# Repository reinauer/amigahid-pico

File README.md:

# amigahid-pico

please note: the interesting stuff goes into the [development](https://github.com/borb/amigahid-pico/tree/development) branch, so if main seems slow, check it out.

## introduction

amigahid-pico uses the rp2040 microcontroller (e.g. the raspberry pi pico) in a carrier board to attach usb input devices to a standard amiga without the need for a usb stack on the amiga itself.

it currently supports keyboards and mice and provides connection via the internal keyboard connector, the rj11/din socket on big-box amigas, and via the controller ports.

**this project is very much a work in progress.**

## **important note**

* r7 uses the native RP2350A/RM2 board and an ALPS menu lever. See [r7 firmware setup](./doc/installation.md#rev7-rp2350a-and-rm2) and [lever controls](./doc/runtime-configuration.md#rev7-menu-lever).
* for r5/r6 carriers on the `features` branch, select `BOARD_HIDPICO_REV5` to enable both controller ports: port 1 defaults to mouse and port 2 to USB joystick. REV4 firmware supports the same keyboard and first port, but leaves the second port unused. see [USB joystick mode](./doc/joystick.md).

* **always read the [errata](./doc/errata.md) section for the current pcb layout before deciding whether or not to build.**

## documentation

* [installation](./doc/installation.md)
* [hardware](./doc/hardware.md)
* [errors in revisions (errata)](./doc/errata.md)

## history

this project is a rewrite of the [amigahid](https://github.com/borb/amigahid) project to the rp2040 microcontroller.

originally, after the retirement of the arduino adk board and shortening availability of the max3421e "usb host shield" for arduino boards, the need for a cheap, easy and continually available replacement was sought.

at first, the uhs mini via a level shifter seemed ideal, but significant issues were found convincing it to work with a variety of arduino boards.

the rp2040 made sense as a target because it is widely available, has sufficient physical connections and is powerful enough to meet multiple needs.

## what is the latency of this?

i have not measured the latency, but the keyboard signals are sent out the moment they are received on the usb bus. the potential latency is likely fractionally longer than the amiga mcu but bear in mind the rp2040 is significantly faster than the standard amiga keyboard controller.

## roadmap

please see the issues tab on the [github repository](https://github.com/borb/amigahid-pico) for the current list of planned features. the tl;dr is:

normal:
* i<sup>2</sup>c display for config/status
* controller emulation
    * keyboard-based controller emulation (use udlr for directions?)
* flash memory-based configuration
* possible amiga-side control panel (using bidirectional controller port signals)
* rotary control simulation (for controlling gotek drives)

crazy talk:
* non-amiga support
* non-hidbp support
* analogue/paddle emulation
* fix some tinyusb issues (hotplug, timing-related instability)

## license

on the fence at the moment, but the current license choice is Eclipse Public License 2.0 (EPL-2.0).

## third party licenses

* µgui: this code contains 'µgui' by achim döbler; the license for this can be read at in the [display readme](./src/display/README.md)

## whuh... who?

nine <[nine@aphlor.org](mailto:nine@aphlor.org)>

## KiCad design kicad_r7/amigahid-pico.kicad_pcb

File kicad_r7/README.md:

# AmigaHID r7 — hardware prototype

Copied from `kicad_r6`. **Prepared for a factory quotation and prototype CAM
review; not released for manufacture.** The r6 project is unchanged.

## Current design

- **70 × 66 mm**, four copper layers, nominal 1 mm PCB. The bounding rectangle is
  2.9% smaller than r6's 70 × 68 mm board. All assembled components are on top.
  The DB9 edge extends 6 mm under the housings; KiCad Y now spans -6..60 mm,
  retaining all component and route coordinates.
- Bare RP2350A, 4 MB Winbond QSPI flash, and left-facing RMC20452T / RM2 radio.
- Centered 35.5 × 33.7 mm OLED, two DE9 ports, mini-DIN keyboard and two stacked
  USB-A ports. The CH334P hub uses two of its four downstream channels.
- USB-C and a side-actuated RECOVERY switch at the bottom right.
- H1–H4 are shared OLED/base/main-PCB mounts. H5/H6, the A500 header, extra power
  header and selector jumper are removed. UART/SWD use bare pads.
- Five-sheet schematic: interfaces, controller, power, USB, and control.

Open [the KiCad project](amigahid-pico.kicad_pro). The normal editable design is
[the schematic](amigahid-pico.kicad_sch) and [the PCB](amigahid-pico.kicad_pcb).
The matching enclosure is in [`../case_r7`](../case_r7/README.md).

## Power and recovery

Mini-DIN pin 4 remains a 5 V power input. The TPS2116 automatically gives
USB-C priority and falls back to the keyboard supply when USB-C is removed.
It has reverse-current blocking, so the two supplies are not directly joined.
See the [TPS2116 datasheet](https://www.ti.com/lit/ds/symlink/tps2116.pdf).
The DE9 5 V pins remain unconnected. No power-selection jumper is needed.

The [A4000 user guide, appendix B-8](https://device.report/m/e9fdb1a480863f0ee437f3aaf1a4cf073445989ed93d380fc9f8956629044f95.pdf#page=85)
rates keyboard power at **100 mA**. The user's current revision operates from
this port; r7 preserves that option, but its new MCU, hub, radio, display and
peripherals require a fresh current measurement. The 500 mA hold PTC is shared
by both USB-A ports and does not establish available Amiga current.

USB-C can also power normal operation from an adequately rated 5 V supply.
Use a supply rated for at least 1 A for prototype testing. This board does not
negotiate USB PD or read Type-C current advertisements. A PC's unconfigured
USB port is not a guaranteed normal-operation power source: hold RECOVERY
before connecting a PC for service. Keyboard-only operation must stay within
the actual Amiga/cable budget; adding USB-C power does not raise that rating.

| State | Action and result |
|---|---|
| Amiga off, PC recovery | Hold RECOVERY, connect USB-C, wait at least 0.1 s, release. |
| USB-C already connected | Press/release RECOVERY to enter ROM recovery. |
| Normal operation from USB-C supply | Connect power without holding RECOVERY. |
| Return to keyboard-powered operation | Remove USB-C, then press/release RECOVERY to reboot normally. |
| Return to USB-C-only normal operation | Unplug/reconnect USB-C without holding RECOVERY. |

Recovery is implemented in hardware. RECOVERY_N low presets the SN74HCS74 latch;
Q2 pulls QSPI-CS low through R6, U7 selects the PC data path, and U11 removes
USB-A power. The Amiga signal switches are disabled whenever keyboard power
is absent or recovery is selected. Thus invalid application flash does not
prevent button-based ROM recovery. This assumes normal RP2350 OTP settings;
permanently disabling ROM USB boot in OTP is outside this prototype design.

U13 (TPS3808G33DBVR) monitors the shared 3.3 V rail and holds RUN low
until the rail exceeds its nominal 3.07 V threshold and the reset-release
delay expires. CT is intentionally unconnected for a nominal 20 ms delay.
C41 provides local 100 nF bypassing; R12 remains the 10 kΩ RUN pull-up.
This allows the external flash to power up before the MCU starts its boot ROM.

The switch grounds RECOVERY_N, pulled up by R26 (10 kΩ). This net drives
both U13's manual-reset input and U9's preset input. U13's automatic reset
output drives RUN only, so cold-start and brownout resets do not themselves
request BOOTSEL. Button release also receives the supervisor's reset delay.
The recovery latch still retains the requested USB mode after release.

The latch uses Schmitt inputs and a separate 100 kΩ/100 nF clear delay. U12 translates
USB VBUS to 3.3 V with power-off protection. At power-up with the button held,
both asynchronous latch inputs can be asserted: the documented state has
both outputs high, while U13 holds RUN low to keep the MCU reset and D2 keeps USB-A power off.
Hold the button until the clear delay has expired, then release. The same
button without USB-C performs a normal reset. There is no firmware timing or
double-tap dependency.

U11 ramps the 220 µF host reservoir with 10 nF on CT (about 26.6 ms typical
10–90% rise at 5 V). Reservoir charging is about 33 mA over that interval,
before peripheral load and tolerances. Recovery leaves this branch off.
Direct USB-C bypass is 4.7 µF + 100 nF; the mux soft-starts the main board
supply. Check actual inrush, recovery current and USB suspend behavior on the
first assembled board. No USB compliance certification is implied.

## Placement and capacitor review — 2026-10-14

The required connectors and OLED stay fixed. U2 moved toward the first DE9
connector; U3 now occupies the MCU's right side. U8 was moved and rotated toward
the stacked USB-A connector. Pull-up arrays and local bypass parts were moved
with the signal groups. The signal-net minimum-spanning-tree estimate fell
from 1904 to 1607 mm (15.6%); this is a placement metric, not measured routed
length, timing or signal-integrity proof.

Most resistors and local bypass capacitors are already **0402**. The OLED
pull-ups and several inherited bypass capacitors use **0603**. The 10 µF supply
capacitors remain **0805**. Replacing all 0805 parts with 0603 would save little
board area and can reduce effective capacitance at operating voltage.

For C10/C11, Samsung's typical 25°C DC-bias curves give:

| Part | Package / rating | Effective pair capacitance at 3.3 V |
|---|---|---|
| Former C59461, CL10A226MQ8NRNC | 0603, 22 µF / 6.3 V | about 19.5 µF |
| Selected C45783, CL21A226MAQNNNE | 0805, 22 µF / 25 V | about 29.8 µF |

These typical values exclude initial tolerance, temperature and aging; they
are not guaranteed minima. The larger parts provide more transient margin.
Sources: [Samsung 0603 curves](https://product.samsungsem.com/mlcc/CL10A226MQ8NRN.do),
[Samsung 0805 curves](https://product.samsungsem.com/mlcc/CL21A226MAQNNN.do), and
[AP63203 application guidance](https://www.diodes.com/datasheet/download/AP63200-AP63201-AP63203-AP63205.pdf).
C3's displayed voltage was also corrected to 25 V to match its existing C15850
part number.

### USB-A bulk capacitor

150 µF is a sensible nominal value: at −20% initial tolerance it gives 120 µF.
The USB hub guidance calls for at least 120 µF of low-ESR reservoir capacitance
per hub; that can be shared by these two adjacent ports on the same power rail.
See [Microchip AN17](https://www.microchip.com/content/dam/mchp/documents/OTH/ApplicationNotes/ApplicationNotes/AN17-APID.pdf).

The former RVT standard electrolytic's supplier table leaves the ESR limit
blank. C4 is upgraded to **220 µF / 10 V polymer, C19270700**, with
specified **35 mΩ at 100 kHz**, in approximately the same 6.6 mm square body
area. Its initial minimum capacitance is 176 µF. It is listed at $0.1657 each
at quantity 5 ($0.1302 at 50), before shipping/taxes, checked 2026-10-14.
[Supplier part](https://www.lcsc.com/product-detail/C19270700.html),
[manufacturer family datasheet](https://datasheet.lcsc.com/datasheet/pdf/25cd8a66a5cec751f287aca4fb3a3d5c.pdf?productCode=C19270700).

C4 remains between the keyboard and stacked USB connectors: their spacing
leaves room for it, and its supply connection can run beside the USB connector.
It does not obstruct the OLED. Rotating the original capacitor into the narrow
gap caused courtyard conflicts; the horizontal orientation is retained.
The supplier lists 5.8 mm height, while the family table shows a 7 mm variant;
confirm the exact ordered part. The case clearance model uses 8 mm, also
covering the 7.72 mm height of the supplier's STEP model.

### Two 12 MHz crystals

Y1 is the RP2350A clock reference and Y2 is the CH334P USB hub reference.
Each passive crystal belongs to a separate on-chip oscillator. Connecting one
crystal to both oscillators is not a valid replacement. A common active clock
would need a clock distribution and startup design; using an MCU-generated
clock would also couple hub operation to firmware/reset behavior.

The WCH datasheet section 6.2 describes a crystal-free mode, but says some
parameters may depart from USB requirements and availability depends on the
ordered variant. Both crystals are retained by the 2026-10-14 design decision.
WCH's v2.91 datasheet specifies approximately 16 pF internally on each XI/XO
pin and recommends no external load capacitors. Matching the selected
10 pF-load crystal still requires allowance for board and pin capacitance.
Sources: [WCH datasheet](https://www.wch.cn/downloads/CH334DS1_PDF.html)
and [RP2350 reference design](https://datasheets.raspberrypi.com/rp2350/hardware-design-with-rp2350.pdf).
C5 provides local 3.3 V ceramic bypass near the USB service circuitry.

A lower-ESR capacitor helps hot-plug droop, but also changes charging inrush.
Measure both USB hot-plug behavior and startup through the actual Amiga cable.
The larger reservoir is behind U11, which disconnects it during recovery.

### Smaller flash option

A 4 × 3 mm USON flash, **W25Q32JVUUIQ / C2999380**, could replace the current
SOIC-8 flash without reducing the 4 MB capacity. Current LCSC listings put it
at about $2.53 versus $1.65 for the selected C5355146 at quantity 1, or $1.91
versus $1.17 at quantity 100. It saves package area but increases BOM cost and
requires a new footprint and routing. The SOIC part is retained because it fits.
Sources: [SOIC flash](https://www.lcsc.com/product-detail/C5355146.html) and
[USON flash](https://www.lcsc.com/product-detail/C2999380.html), checked 2026-10-14.

## Sourcing and footprint provenance

[BOM.csv](BOM.csv) and [SOURCING.csv](SOURCING.csv) list **110 assembled parts** (45 unique LCSC codes).
Every purchased schematic part has an `LCSC Part #` field. Holes and bare test
pads are non-BOM geometry and have no part number. The OLED module and enclosure
hardware are external assemblies, as in r6; the PCB BOM includes J3.
`assembly-accessories.json` specifies the retained r6 SH1106 module and mounting
hardware. The r6 records give its drawings and pinout, but no manufacturer
part number or LCSC code; do not invent a purchasing code or substitute a
GND-first module.

`lcsc.pretty` contains LCSC/EasyEDA imports plus supplier-drawing corrections.
Original imports are retained in `vendor-originals`. The DE9 footprint was
reconstructed from its LCSC supplier drawing because no usable imported model
was available. The local `r7.pretty` library also contains the reset supervisor
and ALPS menu-switch footprints.

Corrections are reproducible in `scripts/prepare_libraries.py`: RM2 pad geometry
and antenna keepout, connector shield pin numbers, USB-C combined power lands,
NPTH locating pegs, stacked USB shield row pitch, and four paste apertures on
the RP2350 exposed land. The MCU's local regulator/decoupling topology follows
the official [RP2350 hardware design reference](https://datasheets.raspberrypi.com/rp2350/hardware-design-with-rp2350.pdf);
its reference PCB and license are in `reference/`.

Factory assembly was selected on 2026-10-14. The public JLC assembly stock
snapshot in [assembly-stock-check.json](assembly-stock-check.json) covers all
43 of the 45 part numbers and records stock at that check. The supervisor
and menu switch need a fresh availability check. Direct retail stock is recorded
separately in [stock-check.json](stock-check.json). Retail unavailability is
not the same as unavailability in the assembler's inventory. These snapshots
are dated evidence, not reserved material or an accepted assembly quote.

| Item | Selected LCSC part | JLC public stock on 2026-10-14 |
|---|---|---:|
| Stacked USB-A | C2341 | 3,310 |
| Mini-DIN | C77848 | 2,060 |
| Two female DE9 connectors | C50380980 | 1,711 |
| RM2 radio | C49451547 | 117 |
| RP2350 regulator inductor | C42411119 | 75 |
| Recovery latch | C2866652 | 619 |

The r6 HOOYA DIN-603 / C7428703 really was stocked in the earlier snapshot.
It now has zero direct LCSC stock and only one in public JLC stock, below the
listed placement minimum. J7 uses **CONNFLY DS1093-01-PN60 / C77848** instead.
Its drawing specifies 1.1 mm signal holes, 2.3 mm shield holes and 13.7 mm shield
spacing. The front face stays at the existing case opening. The supplier
footprint needed corrections to shield-hole size and central-tab position;
these are recorded in `scripts/adopt_connfly_din.py`. C54573054 is a larger
full-size DIN connector, so it is not a substitute for this mini-DIN socket.

Keep the exact Abracon L1: winding polarity is part of the RP2350 regulator
reference layout. The factory's small stock count needs reconfirmation before
ordering. Do not substitute an arbitrary 3.3 µH inductor.

R9's LCSC number was corrected from C25118 (47 Ω) to **C25117 (470 Ω)** to
match the RM2 DOUT-combining circuit. The other selected resistor/capacitor
values were compared with supplier descriptions. D4–D6 add ground-referenced
TPD2EUSB30 ESD protection at both USB-A channels and the USB-C service channel;
these add about $2.05 in initial-tier parts cost. U2/U3 remain cost-review
candidates, but a substitute must retain 5 V signal handling, 3.3 V translation
and specified power-off isolation.

### Stacked USB-A availability and fit

The selected J4 **907-111A1012D10200 / C2341** is available: the direct LCSC
page checked on 2026-10-14 lists **3,310 immediately shippable units**, minimum
and order multiple five, at **$0.1855 each for five** before discounts,
shipping and taxes. The earlier out-of-stock sourcing note has been corrected.
[LCSC listing](https://www.lcsc.com/product-detail/C2341.html).

The board has the drawing's 13.10 mm shield-column pitch, 5.80 mm shield-row
pitch and 2.60 mm contact-row pitch. Shield holes are 2.30 mm; all eight contact holes now use the drawing's
0.92 mm recommendation. The 14.60 mm body width excludes the wider 15.50 +/- 0.20 mm
features. The case opening is now 16.90 mm wide, allowing 0.60 mm per side around
the 15.70 mm maximum envelope. Check retention on the 1 mm PCB too.
[Supplier drawing](https://datasheet.lcsc.com/datasheet/pdf/a0b416dc2d0ad40e281371fbd00e5e99.pdf?productCode=C2341).

The supplier drawing calls the housing high-temperature thermoplastic, while
the LCSC Chinese product description says it is not high-temperature rated.
Neither establishes a soldering temperature/time profile. Plan separate
through-hole assembly after SMT reflow unless the supplier confirms a suitable
profile. [LCSC Chinese listing](https://item.szlcsc.com/2717.html).

## Review results and remaining order gates

The final configured KiCad checks report **zero ERC violations, zero DRC
violations, zero unconnected items and zero schematic parity issues**.
`scripts/audit_board.py` additionally checks all 110 purchased parts are on top,
all have project-relative models, the 70 × 66 mm outline, connector drills,
absence of bottom silkscreen and absence of L3 signal crossings beneath the
bottom USB pairs. USB layer transitions have ground holes within 2 mm.
L2 contains no signal tracks. These checks are not measured signal integrity.

The explicit **JLC04101H-7628 nominal 1 mm** stackup is recorded in the board.
Main outer USB pairs use 0.2474 mm width / 0.1501 mm gap for the calculator's
90 Ω target; short pad escapes and the USB2 connector neck use narrower copper.
The fabricator must confirm the construction and impedance. The filled L3
plane was inspected after moving the control routes out of the USB corridor.

Both case halves rebuild as closed, single-solid meshes. The modeled hardware
intersection is empty, including the new USB shield-tail floor pockets. This
is a nominal geometry check; connector retention, tolerance and actual fit
still need the first assembled board. The retained r6 OLED drawings are in
`../case_r7/reference/`, with the same 3V3–GND–SCL–SDA pin order.

**Specify epoxy-filled, copper-capped electrical vias (IPC-4761 Type VII).**
The layout has thermal and other vias in or close to solder lands. Tenting
alone does not prevent solder loss there. Connector and mounting holes must
remain open. The native PCB and exported via list identify the holes to fill.
This can increase four-layer fabrication cost; obtain a quote for this exact
process, nominal 1 mm thickness and ENIG. See [JLC via covering guidance](https://jlcpcb.com/help/article/pcb-via-covering)
and [manufacturing-requirements.json](manufacturing-requirements.json).

Before ordering, obtain the factory's acceptance of:

1. The stackup, filled/capped via process, impedance target and thickness.
2. All 45 part numbers, actual batch allocation, placement minima and attrition.
3. Factory through-hole soldering after SMT reflow, 1 mm connector retention,
   and a placement preview confirming the explicit JLC rotations and polarity.
4. Installation of the retained r6 OLED and specified nylon hardware.

The local `production/factory-review-*.zip` package contains Gerbers, separate
plated/nonplated drills, IPC-D-356 netlist, BOM, corrected JLC CPL, via list,
editable KiCad sources, schematic/layer PDFs, board STEP and case STL files.
It is marked for quotation/CAM review, pending manufacturing acceptance.

### Assembly export defaults

Identical purchased parts now have identical Value, Footprint and LCSC fields.
Circuit roles such as CC1, BOOTSEL and hub decoupling are in the separate
`Function` field. Fabrication Toolkit therefore emits **45 BOM rows for 110
components**, without splitting identical LCSC parts across multiple rows.

The project saves **Apply automatic translations = off** in
`fabrication-toolkit-options.json`. Each assembled symbol and PCB footprint has
an explicit `FT Rotation Offset` from `assembly-orientation.json`. Do not turn
generic translations back on: its package-name rules rotate these LCSC parts
incorrectly. This is the documented [Fabrication Toolkit field mechanism](https://github.com/bennymeg/Fabrication-Toolkit#attributes).

The audit corrected the exported rotations of U1, U2, U3, U5, U8, U9, U11,
U12 and Q1-Q3, plus L1's dotted end and D3's cathode. D2 is correct with its
cathode toward the bottom edge. The L1 and D3 STEP orientations also now match
the physical pins. Twenty-five footprints have physical pin-1 dots, cathode
bars or a positive-terminal mark on top silkscreen; the numbered-pad drawing
is `production/assembly-orientation.svg`.

Regenerate manufacturing files from the checked board before ordering.
Existing stock/rotation snapshots do not cover the supervisor and menu switch.
Check U13 pin 1 and SW2 contact orientation in the factory placement preview.

For a new upload use `production/gerbers.zip`, `production/bom.csv` and
`production/positions.csv`, generated together after the checks below.
The current browser order retains its earlier upload and manual corrections;
local exports do not change that order. RM2 and DE9 lack useful JLC placement
models, so factory CAM must use the supplier drawings and numbered pads.

[Electrical review and prototype test plan](electrical-review.json) records
startup, recovery, source takeover, backfeed, inrush and voltage-budget review.
In particular, the shared PTC is not a precise 500 mA current limiter and does
not guarantee 500 mA at either USB port. At 0.5 A its specified 0.70 Ω maximum
post-trip resistance alone would lose 0.35 V; switches, cable and copper add
further loss. Establish the intended load from measurements.

The first order should be a small prototype batch. Build the
[`BOARD_HIDPICO_REV7` firmware](../doc/installation.md#rev7-rp2350a-and-rm2), then test
USB-C-only recovery with invalid flash, two peripherals, Amiga supply
current/droop/backfeed, radio operation and case fit. The firmware has not
been physically validated on r7.

### Cost discussion

The public assembly snapshot gives **$23.7146 per board** at initial part-price
tiers. This excludes OLED, mounting hardware, PCB, assembly/setup, case,
shipping and tax; it is not a factory quote. The RM2 is about $6.53, the two
interface buffers total $4.07, and the three USB protectors total $2.05.
The buffers and protection parts are useful future cost-review candidates,
provided replacements preserve voltage tolerance, power-off isolation and ESD
performance. Both independent crystals and the current SOIC flash are retained.
Factory setup and filled-via charges may matter more for a small batch than
minor resistor/capacitor savings.

## Rebuilding and validation boundaries

`circuit.json` is the source for `scripts/build_schematic.py`, which regenerates
the schematic and BOM. `scripts/build_board.py` creates a **fresh placement and
overwrites routing**. `scripts/prepare_routing.py` adds reviewed local routing
once to that fresh board. Do not rerun these board builders on hand-edited
routing without retaining a backup. `scripts/configure_rules.py` sets the board
constraints and power net classes.

Run `scripts/audit_board.py`, `scripts/check_reset.py` and
`scripts/check_menu.py` with pcbnew Python
after filling zones. The reset check verifies the supervisor pinout and keeps
automatic RUN resets separate from the manual recovery request. Run KiCad
ERC and DRC with schematic parity, then `scripts/export_factory_review.py`
with pcbnew Python to
export the quotation package; it refuses stale checks or reported violations.
The current outputs live in `review/` and `production/`. Refresh these after
any change. The JSON ERC/DRC reports list configured ignored checks, including
library footprint filters, missing courtyards and tuning-profile geometry;
there are no per-item DRC exclusions. Copper clearances and connectivity remain
enabled. DRC does not prove electrical correctness or physical fit.

USB recovery current/suspend behavior, clock startup, RF behavior, two-device
operation, Amiga backfeed isolation and connector insertion forces require the
hardware tests in `electrical-review.json`.

### Cold-start reset verification

The supervisor threshold and delay follow the
[TI TPS3808 datasheet](https://www.ti.com/lit/ds/symlink/tps3808.pdf).
The selected W25Q32JV requires 20 µs from VCC(min) to chip select going low.
Check +3V3 at the flash, RUN, RECOVERY_N and QSPI-CS on an oscilloscope:
normal keyboard-powered and USB-C-powered starts must boot application flash;
held RECOVERY with USB-C must enter ROM recovery. Repeat with slow supply ramps,
short power interruptions and source handover. Supervisor addition has not
been physically validated.

### Menu lever wiring and assembly

SW2 is an [ALPS SLLB510100](https://tech.alpsalpine.com/e/products/detail/SLLB510100/)
on the USB-C edge, aligned with the case slot at X=35 mm. Terminal C and the
mechanical anchors connect to ground. The three contacts are active low:

| Contact | Net | RP2350 GPIO | Pull-up |
|---|---|---|---|
| 1 / CCW | MENU_LEFT_N | 14 | R27, 10 kΩ to 3.3 V |
| 2 / CW | MENU_RIGHT_N | 15 | R28, 10 kΩ to 3.3 V |
| T / push | MENU_PUSH_N | 16 | R29, 10 kΩ to 3.3 V |

The REV7 firmware debounces these contacts and provides
[lever menu controls](../doc/runtime-configuration.md#rev7-menu-lever). RECOVERY remains a
separate hardware function. With the board powered, check each input is high
at rest and goes low only for its corresponding action before enabling menu
operation. Confirm the desired left/right sense with the assembled enclosure.

The switch footprint/model originated in the
[JLCEDA](https://lceda.cn/)/[EasyEDA Official Library](https://easyeda.com/),
part C125039. The four signal/common lands use the ALPS 1.0 × 1.6 mm dimensions;
the two 1.1 mm locator holes are unplated. The courtyard reserves the case's
conservative 14.2 × 9.5 mm motion envelope with 0.1 mm assembly clearance.
Check the supplier drawing and a physical sample before production.
The project-relative WRL model has a -0.2 mm Z correction to put the body top
at 2.2 mm and the locating lugs 0.6 mm below the seating plane. The importer's
untransformed STEP is deliberately not used; check exported factory 3D files
for the switch rather than assuming WRL inclusion in a STEP export.

The power components leave this movement envelope clear. Verify regulator
startup, ripple and load transients on the revised placement. Procurement
stock and tape orientation for C125039 still require factory confirmation.

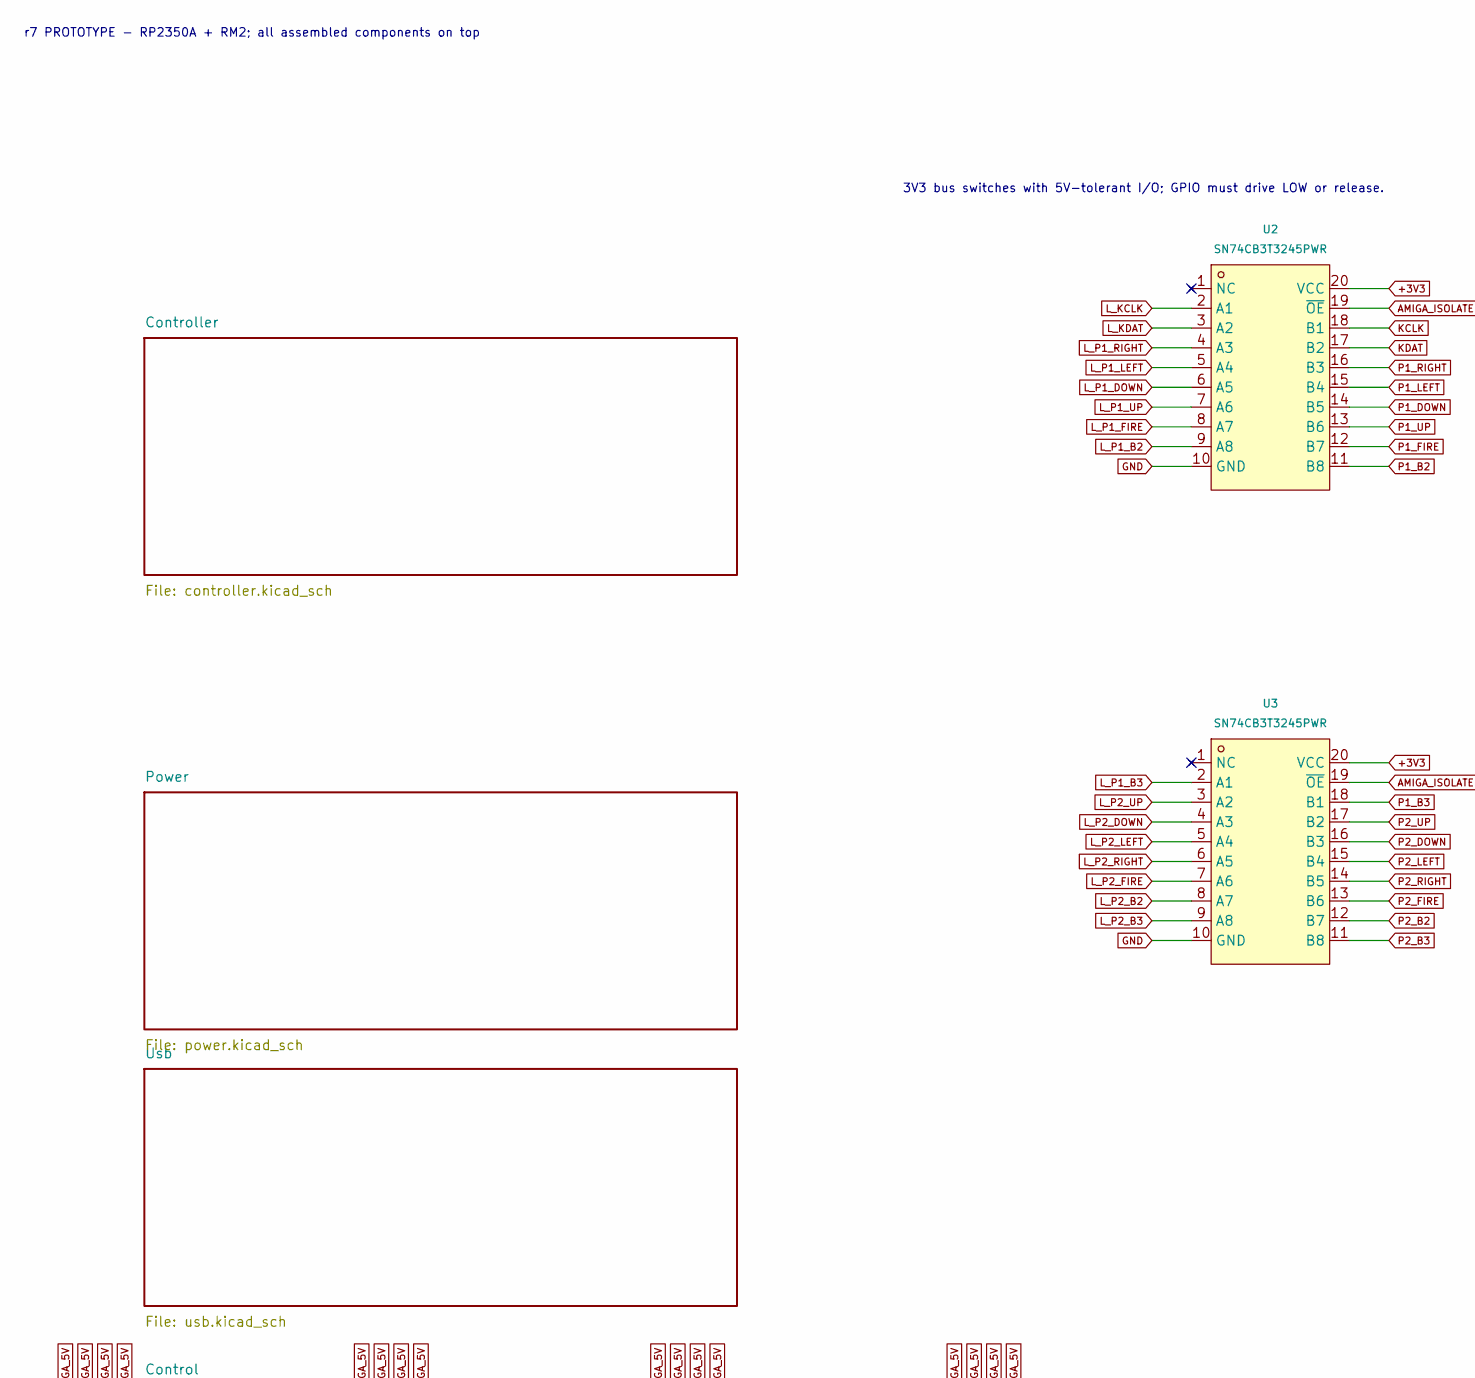
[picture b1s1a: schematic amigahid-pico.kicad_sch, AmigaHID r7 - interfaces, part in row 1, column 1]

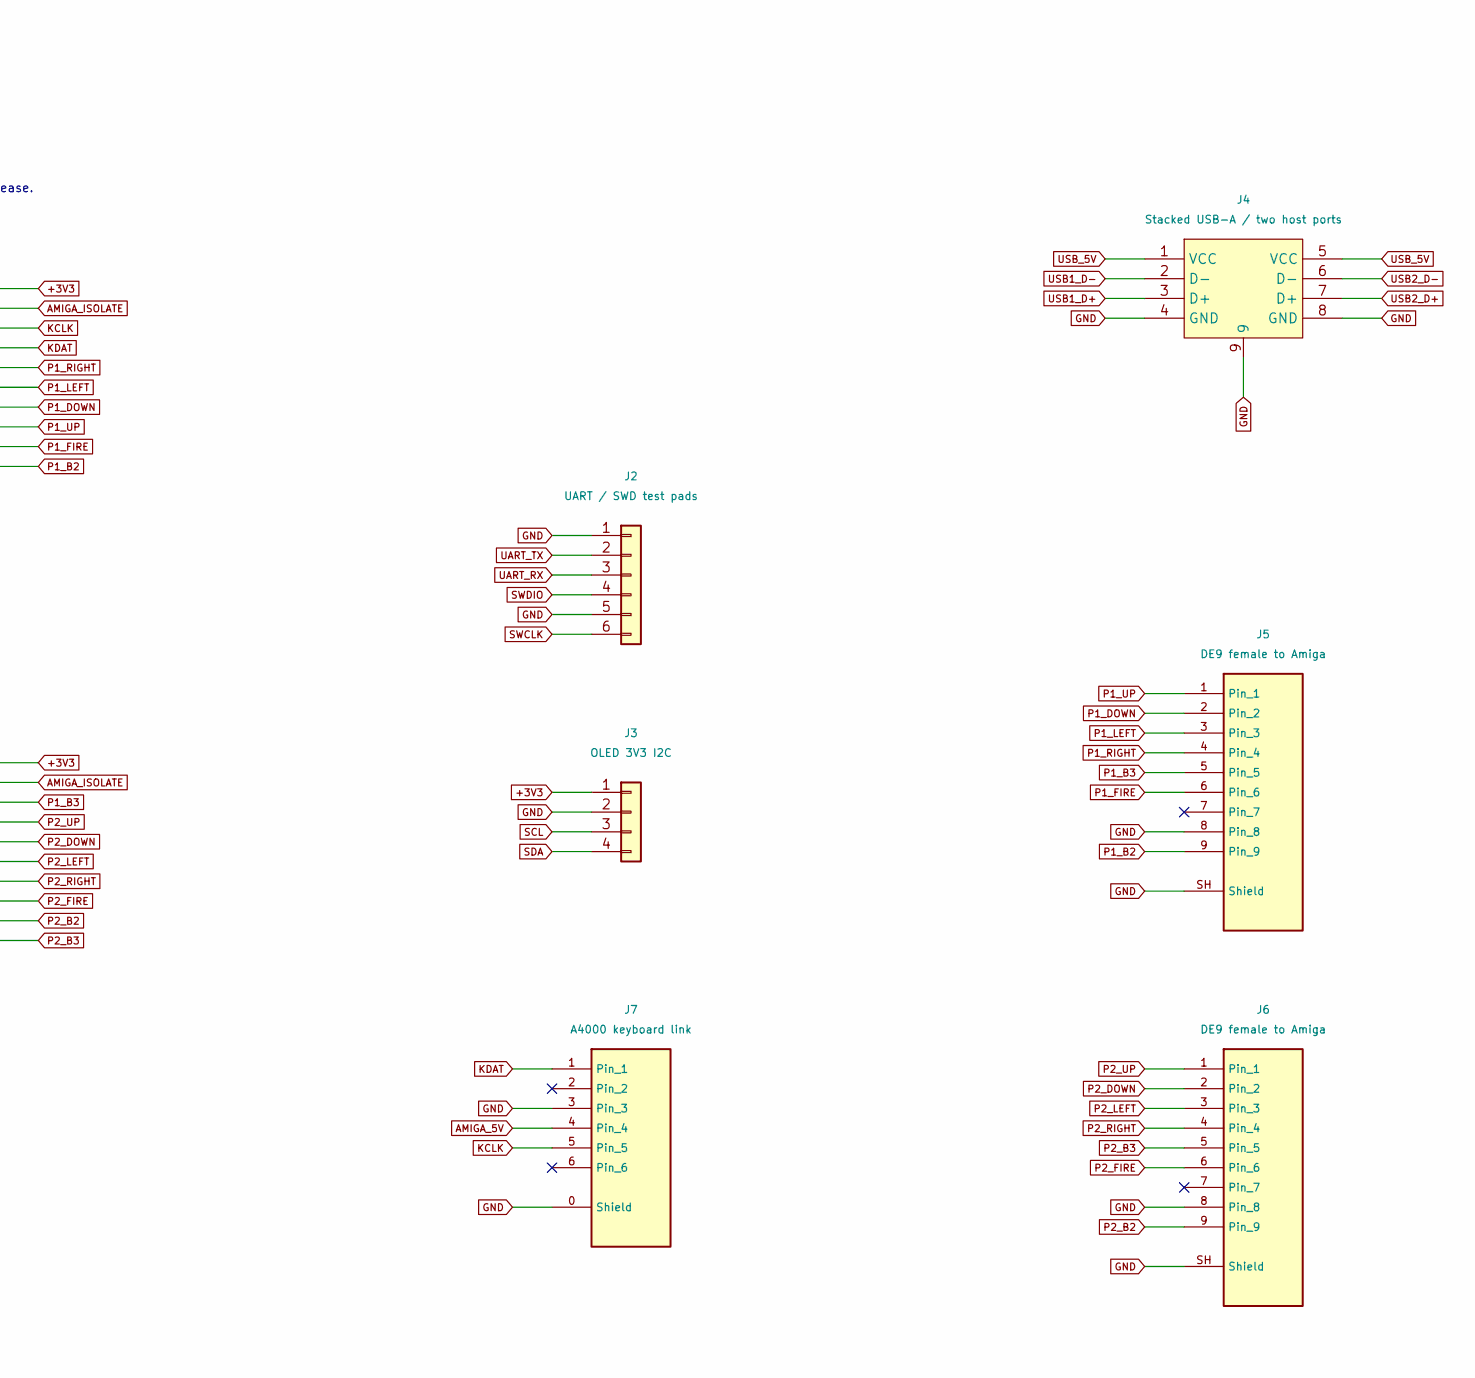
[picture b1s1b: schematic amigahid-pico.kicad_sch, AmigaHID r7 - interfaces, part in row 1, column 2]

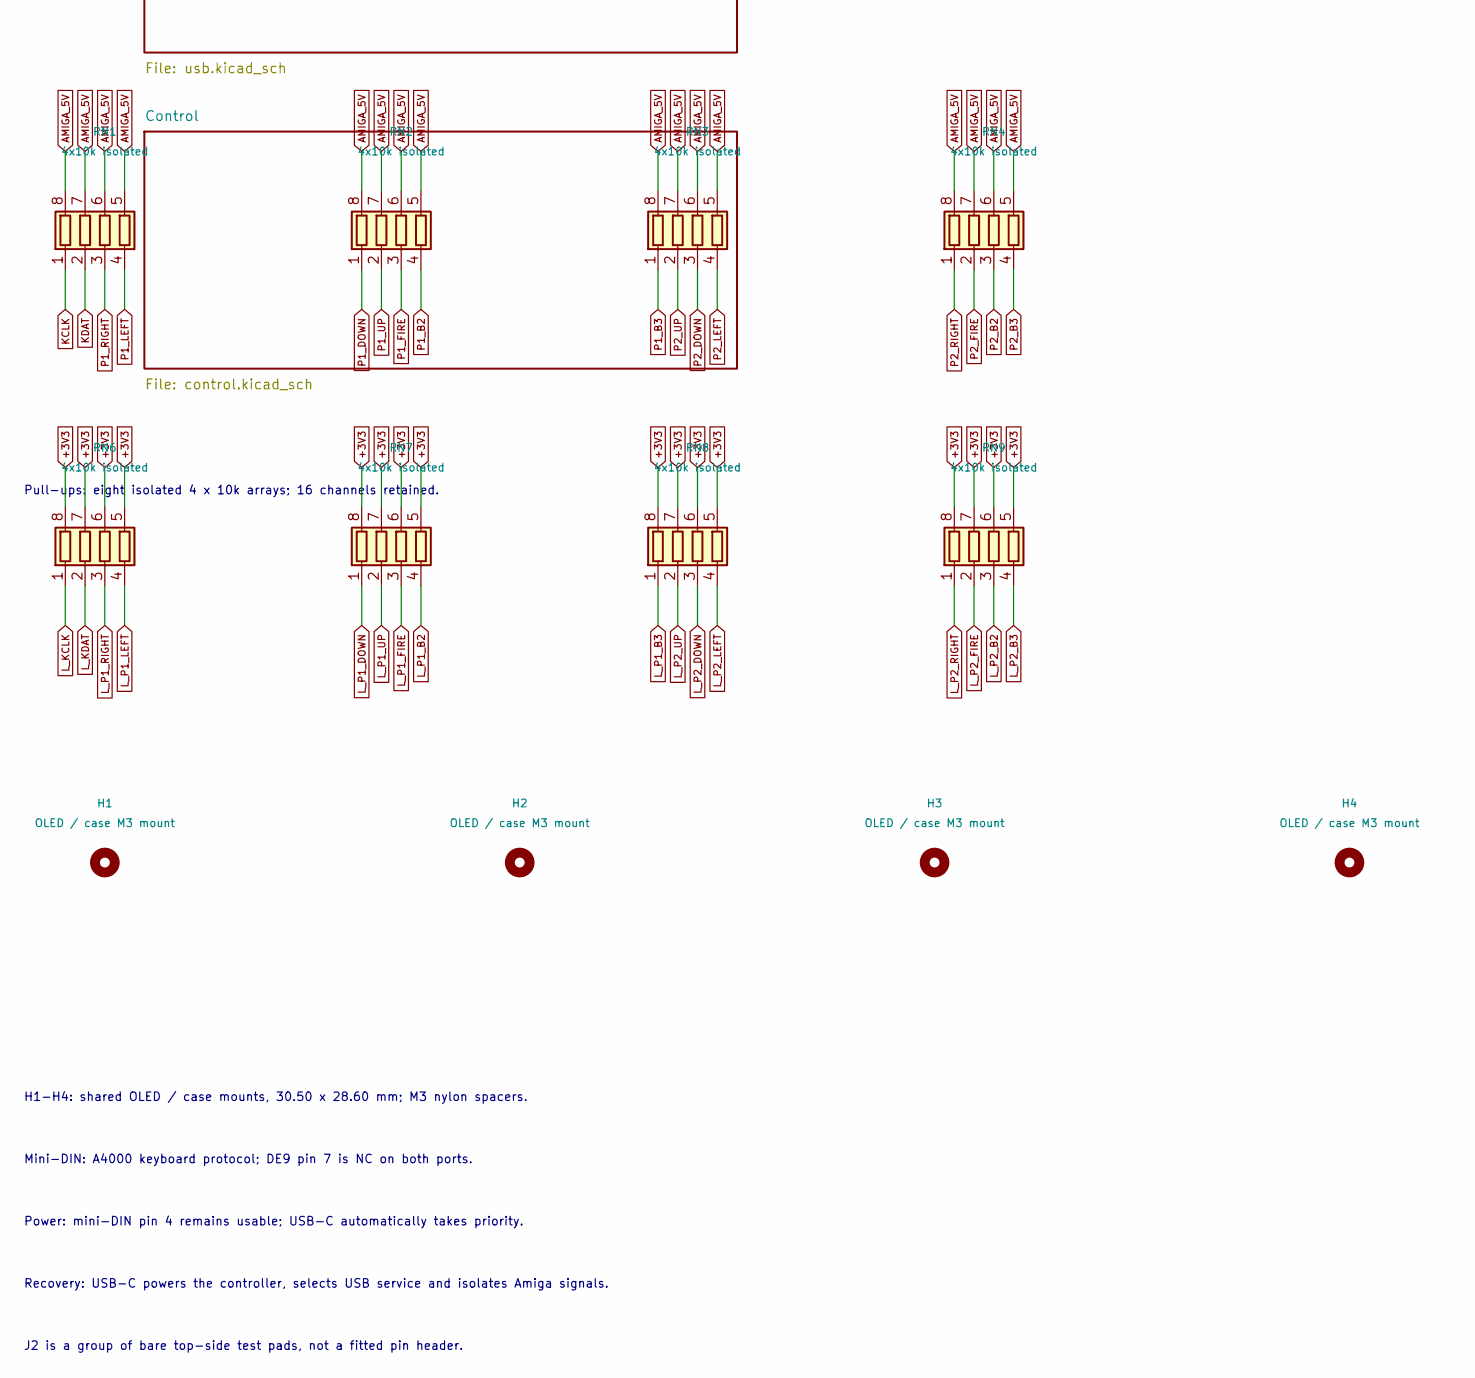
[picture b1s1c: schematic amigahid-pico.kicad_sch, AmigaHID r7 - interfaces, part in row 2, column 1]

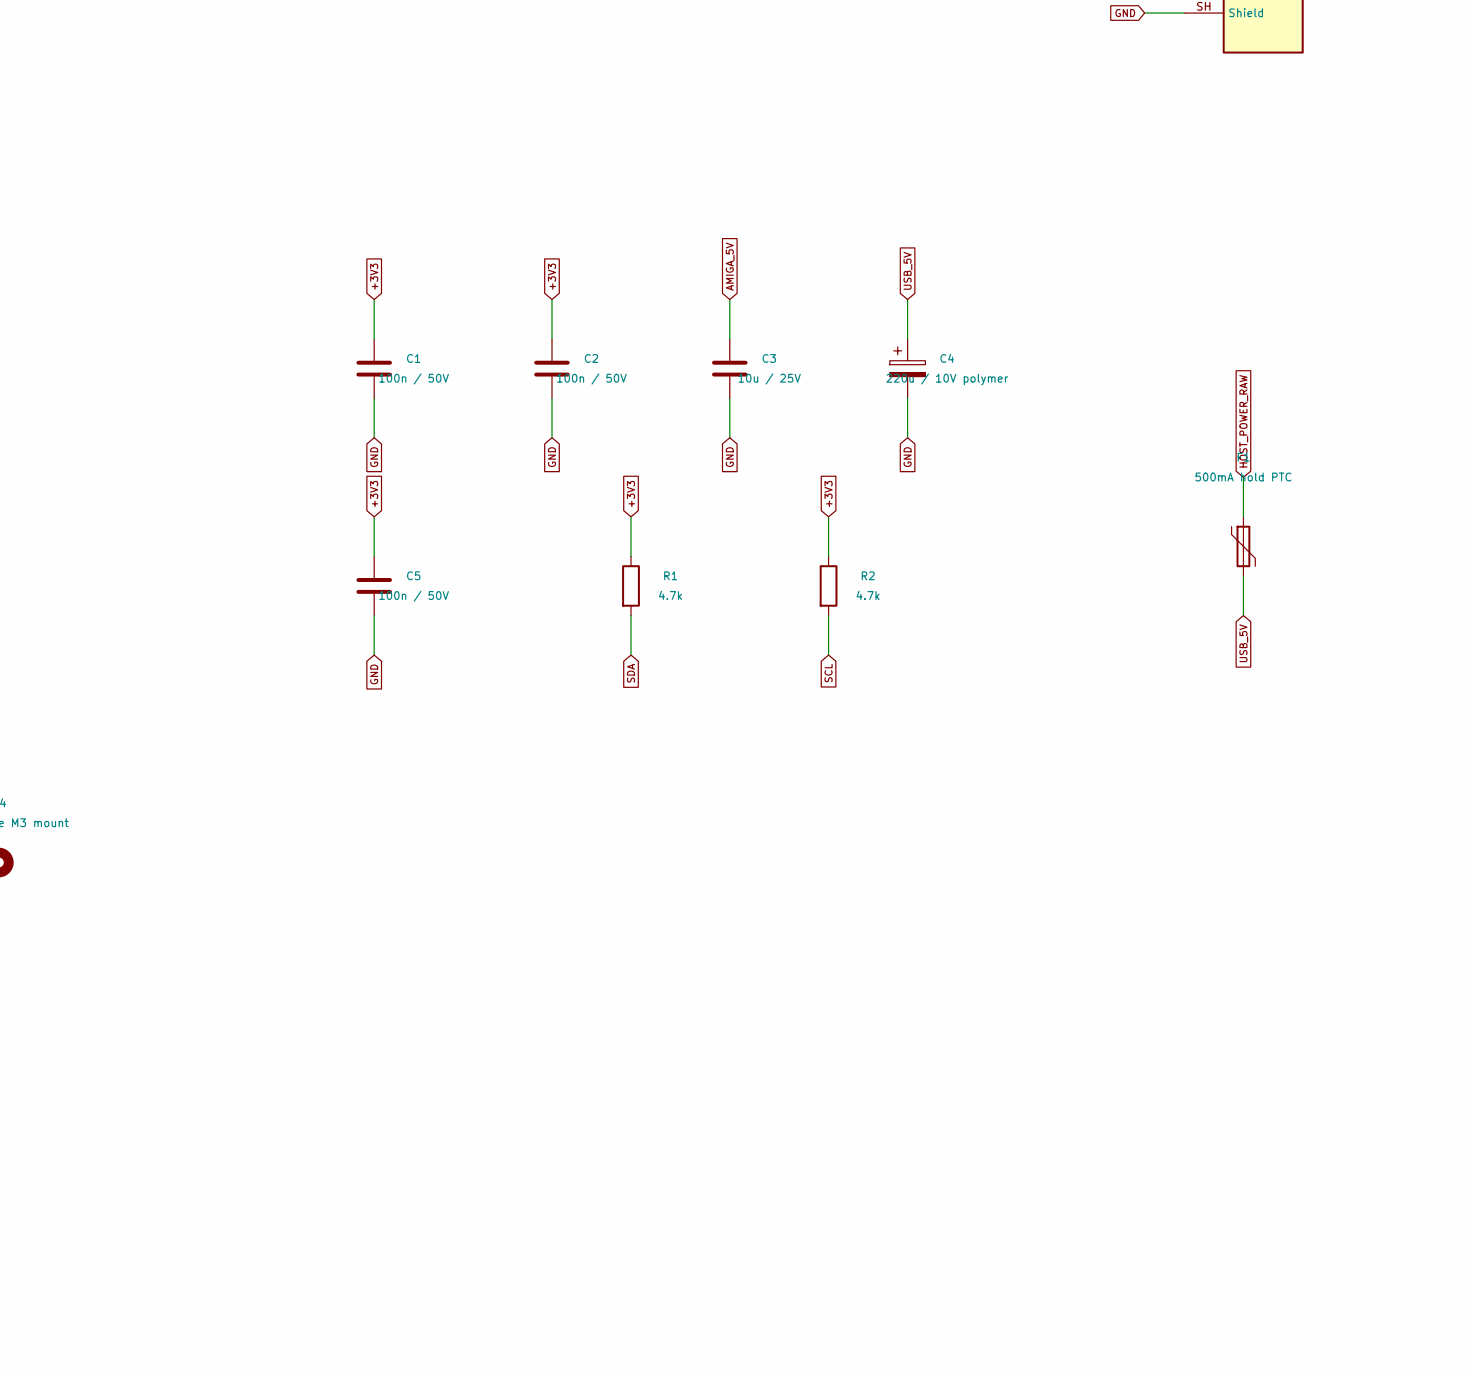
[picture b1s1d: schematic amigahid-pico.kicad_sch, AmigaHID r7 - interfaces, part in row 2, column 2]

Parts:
C1, C2, C5: 100n / 50V; C0603; MPN CC0603KRX7R9BB104; LCSC Part # C14663
C3: 10u / 25V; C0805; MPN CL21A106KAYNNNE; LCSC Part # C15850
C4: 220u / 10V polymer; CAP-SMD_BD6.3-L6.6-W6.6-LS7.4-FD; MPN JBLM2221M010C058RTM; LCSC Part # C19270700
F1: 500mA hold PTC; F1206; MPN MF-NSMF050-2; LCSC Part # C75464
H1, H2, H3, H4: OLED / case M3 mount; MountingHole_3.2mm_M3
J2: UART / SWD test pads; UART_SWD_TestPads
J3: OLED 3V3 I2C; HDR-TH_4P-P2.54-V-F; MPN DS1023-1x4SF11; LCSC Part # C7509546
J4: Stacked USB-A / two host ports; USB-A-TH_USB-M-51; MPN 907-111A1012D10200; LCSC Part # C2341
J5, J6: DE9 female to Amiga; DE9_Female_C50380980; MPN LCK-205A09FJ2A00B1A; LCSC Part # C50380980
J7: A4000 keyboard link; CONN-TH_DS1093-01-PN60; MPN DS1093-01-PN60; LCSC Part # C77848
R1, R2: 4.7k; R0603; MPN 0603WAF4701T5E; LCSC Part # C23162
RN1, RN2, RN3, RN4, RN6, RN7, RN8, RN9: 4x10k isolated; RES-ARRAY-SMD_0603-8P-L3.2-W1.6-BL; MPN EXB38V103JV; LCSC Part # C192513
U2, U3: SN74CB3T3245PWR; TSSOP-20_L6.5-W4.4-P0.65-LS6.4-BL; MPN SN74CB3T3245PWR; LCSC Part # C15298

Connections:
+3V3: C1.1, C2.1, C5.1, J3.1, R1.1, R2.1, RN6.5 (R4.2), RN6.6 (R3.2), RN6.7 (R2.2), RN6.8 (R1.2), RN7.5 (R4.2), RN7.6 (R3.2), RN7.7 (R2.2), RN7.8 (R1.2), RN8.5 (R4.2), RN8.6 (R3.2), RN8.7 (R2.2), RN8.8 (R1.2), RN9.5 (R4.2), RN9.6 (R3.2), RN9.7 (R2.2), RN9.8 (R1.2), U2.20 (VCC), U3.20 (VCC); also elsewhere on the board
AMIGA_5V: C3.1, J7.4, RN1.5 (R4.2), RN1.6 (R3.2), RN1.7 (R2.2), RN1.8 (R1.2), RN2.5 (R4.2), RN2.6 (R3.2), RN2.7 (R2.2), RN2.8 (R1.2), RN3.5 (R4.2), RN3.6 (R3.2), RN3.7 (R2.2), RN3.8 (R1.2), RN4.5 (R4.2), RN4.6 (R3.2), RN4.7 (R2.2), RN4.8 (R1.2); also elsewhere on the board
AMIGA_ISOLATE: U2.19 (~OE), U3.19 (~OE); also elsewhere on the board
GND: C1.2, C2.2, C3.2, C4.2, C5.2, J2.1, J2.5, J3.2, J4.4 (GND), J4.8 (GND), J4.9, J5.8, J5.SH (Shield), J6.8, J6.SH (Shield), J7.0 (Shield), J7.3, U2.10 (GND), U3.10 (GND); also elsewhere on the board
HOST_POWER_RAW: F1.1; also elsewhere on the board
KCLK: J7.5, RN1.1 (R1.1), U2.18 (B1)
KDAT: J7.1, RN1.2 (R2.1), U2.17 (B2)
L_KCLK: RN6.1 (R1.1), U2.2 (A1); also elsewhere on the board
L_KDAT: RN6.2 (R2.1), U2.3 (A2); also elsewhere on the board
L_P1_B2: RN7.4 (R4.1), U2.9 (A8); also elsewhere on the board
L_P1_B3: RN8.1 (R1.1), U3.2 (A1); also elsewhere on the board
L_P1_DOWN: RN7.1 (R1.1), U2.6 (A5); also elsewhere on the board
L_P1_FIRE: RN7.3 (R3.1), U2.8 (A7); also elsewhere on the board
L_P1_LEFT: RN6.4 (R4.1), U2.5 (A4); also elsewhere on the board
L_P1_RIGHT: RN6.3 (R3.1), U2.4 (A3); also elsewhere on the board
L_P1_UP: RN7.2 (R2.1), U2.7 (A6); also elsewhere on the board
L_P2_B2: RN9.3 (R3.1), U3.8 (A7); also elsewhere on the board
L_P2_B3: RN9.4 (R4.1), U3.9 (A8); also elsewhere on the board
L_P2_DOWN: RN8.3 (R3.1), U3.4 (A3); also elsewhere on the board
L_P2_FIRE: RN9.2 (R2.1), U3.7 (A6); also elsewhere on the board
L_P2_LEFT: RN8.4 (R4.1), U3.5 (A4); also elsewhere on the board
L_P2_RIGHT: RN9.1 (R1.1), U3.6 (A5); also elsewhere on the board
L_P2_UP: RN8.2 (R2.1), U3.3 (A2); also elsewhere on the board
P1_B2: J5.9, RN2.4 (R4.1), U2.11 (B8)
P1_B3: J5.5, RN3.1 (R1.1), U3.18 (B1)
P1_DOWN: J5.2, RN2.1 (R1.1), U2.14 (B5)
P1_FIRE: J5.6, RN2.3 (R3.1), U2.12 (B7)
P1_LEFT: J5.3, RN1.4 (R4.1), U2.15 (B4)
P1_RIGHT: J5.4, RN1.3 (R3.1), U2.16 (B3)
P1_UP: J5.1, RN2.2 (R2.1), U2.13 (B6)
P2_B2: J6.9, RN4.3 (R3.1), U3.12 (B7)
P2_B3: J6.5, RN4.4 (R4.1), U3.11 (B8)
P2_DOWN: J6.2, RN3.3 (R3.1), U3.16 (B3)
P2_FIRE: J6.6, RN4.2 (R2.1), U3.13 (B6)
P2_LEFT: J6.3, RN3.4 (R4.1), U3.15 (B4)
P2_RIGHT: J6.4, RN4.1 (R1.1), U3.14 (B5)
P2_UP: J6.1, RN3.2 (R2.1), U3.17 (B2)
SCL: J3.3, R2.2; also elsewhere on the board
SDA: J3.4, R1.2; also elsewhere on the board
SWCLK: J2.6; also elsewhere on the board
SWDIO: J2.4; also elsewhere on the board
UART_RX: J2.3; also elsewhere on the board
UART_TX: J2.2; also elsewhere on the board
USB1_D+: J4.3 (D+); also elsewhere on the board
USB1_D-: J4.2 (D-); also elsewhere on the board
USB2_D+: J4.7 (D+); also elsewhere on the board
USB2_D-: J4.6 (D-); also elsewhere on the board
USB_5V: C4.1, F1.2, J4.1 (VCC), J4.5 (VCC)

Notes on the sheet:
r7 PROTOTYPE - RP2350A + RM2; all assembled components on top
3V3 bus switches with 5V-tolerant I/O; GPIO must drive LOW or release.
Pull-ups: eight isolated 4 x 10k arrays; 16 channels retained.
H1-H4: shared OLED / case mounts, 30.50 x 28.60 mm; M3 nylon spacers.
Mini-DIN: A4000 keyboard protocol; DE9 pin 7 is NC on both ports.
Power: mini-DIN pin 4 remains usable; USB-C automatically takes priority.
Recovery: USB-C powers the controller, selects USB service and isolates Amiga signals.
J2 is a group of bare top-side test pads, not a fitted pin header.
